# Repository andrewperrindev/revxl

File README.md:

# The RevXL Keyboard

The RevXL is a maximalist Reviung-inspired ergonomic keyboard with per-key RGB LEDs, an OLED display, a rotary encoder, and a breakaway arrow cluster. It’s powered by a wired RP2040 microcontroller with QMK and Vial handling things on the firmware side. At its core, the RevXL is designed to be an on ramp to the ergonomic mechanical keyboard space. It shows off the scene’s most catchy bells and whistles while still providing a few creature comforts of more traditional layouts.

## Sponsored By PCBWay

This project is sponsored by [PCBWay](https://www.pcbway.com). They're the internet's premier PCB fabricator and are a one-stop-shop for all your prototyping needs. They offer PCB fabrication services, 3D printing with a variety of materials, and even PCBA assembly services for those of you who prefer not to solder their own projects. If it can be represented as a design file, you can probably upload it to [PCBWay](https://www.pcbway.com) and receive it a few days later in the mail.

PCBWay did a great job manufacturing the RevXL PCB. The order shipped quickly, and all of the PCBs arrived safe and sound inside of a well packed box and vacuum sealed bubbled wrap. My thanks to [PCBWay](https://www.pcbway.com) for helping to make this keyboard a reality.

## Ergogen Layout

The RevXL was designed with the Ergogen keyboard layout generator. The techniques used here are similar to those I detailed in my [Ergogen tutorial series](https://flatfootfox.com/ergogen-introduction/). The largest new additions were the considerations needed for the per-key RGB LEDs and the breakaway arrow cluster.

## Custom Keycaps

I needed to order a few additional keycaps from [FK Caps](https://fkcaps.com/?a=FlatFootFox) to fill out the arrow key cluster. I decided to use that was an excuse to create a whole custom keycap layout. It's based around a minimalist 3x3 pixel font. You can *just* make out the key glyphs if you squint.

## Build of Materials

| Part                         | Amount | Price           | Link                                                 |
| ---------------------------- | ------ | --------------- | ---------------------------------------------------- |
| Revxl PCB via PCBWay         | 1      | $60.00 USD Shipped | https://github.com/ImStuBTW/revxl                    |
| RP2040 "Pro Micro"           | 1      | $3.00 USD       | https://www.aliexpress.us/item/3256806423363289.html |
| Choc Switches                | 68     | $40.00 USD      | https://www.aliexpress.us/item/3256805697157410.html |
| 1N4148 T4 Diodes             | 68     | $2.00 USD       | https://www.aliexpress.us/item/2255800498728983.html |
| SK6812 MINI-E RGB LEDs       | 68     | $2.00 USD       | https://www.aliexpress.us/item/2255800498728983.html |
| EC11 Rotary Encoder          | 1      | $2.50 USD       | https://www.aliexpress.us/item/2255800160725313.html |
| EC11 20x15mm Knob            | 1      | $3.00 USD       | https://www.aliexpress.us/item/2251832562966356.html |
| MBK Glow Keycaps             | 1      | $55.00 USD      | https://lowprokb.ca/collections/keycaps/products/mbk-glow-r2-keycap-sets |
| 6mm x 3mm x 4.3mm Pushbutton | 1     | $2.00 USD       | https://www.aliexpress.us/item/3256801663262003.html |
| Machine Pins                 | 35     | $6.00 USD       | https://www.aliexpress.us/item/3256801663262003.html |
| Machine Pin Headers          | 39     | $4.00 USD       | https://www.aliexpress.us/item/3256801663262003.html |
| 4mm M2 Screws                | 8      | $1.00 USD       | https://www.aliexpress.us/item/2255801062616407.html |
| 2mm M2 Screw Inserts         | 8      | $1.50 USD       | https://www.aliexpress.us/item/3256804349544912.html |
| Bumpons                      | 1 Pack | $1.00 USD       | https://www.aliexpress.us/item/3256804119199524.html |

# References and Footprints

The [Reviung](https://github.com/gtips/reviung) layout concept was based after gtips' original design. The split thumb design was inspired heavily by Pete Johanson's [revxlp](https://gitlab.com/lpgalaxy/revxlp). For a similar keyboard design available in kit form without the arrow keys, please check out 42Keeb's excellent [Rev57LP](https://42keebs.eu/shop/kits/pro-micro-based/rev57lp-50-low-profile-hotswap-ergo-kit/). They've added RGB LED support in the time it took me to create this keyboard.

The breakaway arrow cluster concept was inspired by the Afternoon Labs [Breeze](https://www.afternoonlabs.com/breeze/) keyboard.

Thanks to Moonbase for the [pixel font breakdown](https://moonbench.xyz/projects/tiny-pixel-art-fonts/)! 

Cheers to Ceoloide's [Ergogen-Footprints](https://github.com/ceoloide/ergogen-footprints) repo. There's more elegant ways of including it as a local git submodule. I may have just chucked their diode, display, LED, reset switch, rotary encoder, and Choc switch footprints into my `/footprints` folder.

The RP2040 footprint was based off rroel's [KiCAD footprint](https://github.com/rroels/kicad_pro_micro_rp2040).

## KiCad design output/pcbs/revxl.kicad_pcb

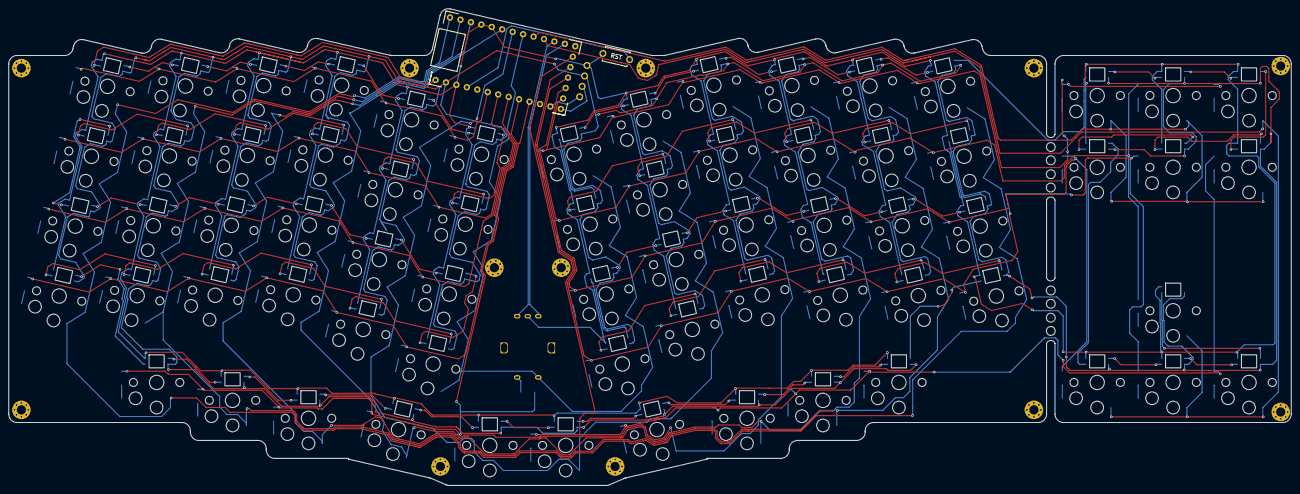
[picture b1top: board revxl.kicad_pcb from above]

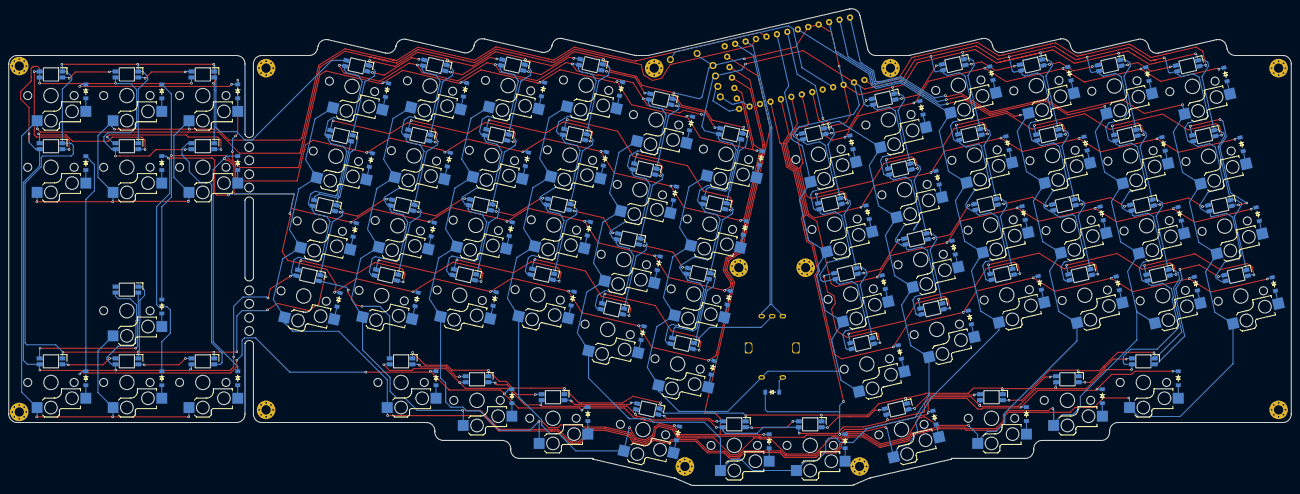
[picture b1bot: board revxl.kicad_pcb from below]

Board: 2 copper layers, 304.0 x 113.0 mm, 228 parts (205 on the bottom side), 156 nets.

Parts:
D1, D2, D3, D4, D5, D6, D7, D8, D9, D10, D11, D12, D13, D14, D15, D16, D17, D18, D19, D20, D21, D22, D23, D24, D25, D26, D27, D28, D29, D30, D31, D32, D33, D34, D35, D36, D37, D38, D39, D40, D41, D42, D43, D44, D45, D46, D47, D48, D49, D50, D51, D52, D53, D54, D55, D56, D57, D58, D59, D60, D61, D62, D63, D64, D65, D66, D67, D68, D69: diode_tht_sod123
DISP1: display_ssd1306
LED1, LED2, LED3, LED4, LED5, LED6, LED7, LED8, LED9, LED10, LED11, LED12, LED13, LED14, LED15, LED16, LED17, LED18, LED19, LED20, LED21, LED22, LED23, LED24, LED25, LED26, LED27, LED28, LED29, LED30, LED31, LED32, LED33, LED34, LED35, LED36, LED37, LED38, LED39, LED40, LED41, LED42, LED43, LED44, LED45, LED46, LED47, LED48, LED49, LED50, LED51, LED52, LED53, LED54, LED55, LED56, LED57, LED58, LED59, LED60, LED61, LED62, LED63, LED64, LED65, LED66, LED67, LED68: led_SK6812mini-e (per-keysingle-side)
RE1: rotary_encoder_ec11_ec12
RST1: reset_switch_tht_top
S1, S2, S3, S4, S5, S6, S7, S8, S9, S10, S11, S12, S13, S14, S15, S16, S17, S18, S19, S20, S21, S22, S23, S24, S25, S26, S27, S28, S29, S30, S31, S32, S33, S34, S35, S36, S37, S38, S39, S40, S41, S42, S43, S44, S45, S46, S47, S48, S49, S50, S51, S52, S53, S54, S55, S56, S57, S58, S59, S60, S61, S62, S63, S64, S65, S66, S67, S68: switch_choc_v1_v2
_1, _2, _3, _4, _5, _6, _7, _8, _9, _10, _11, _12, _13, _14, _15, _16, _17, _18, _19, _20: MountingHole_2.2mm_M2_Pad_Via

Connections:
GND: DISP1.4, LED1.3, LED2.3, LED3.3, LED4.3, LED5.3, LED6.3, LED7.3, LED8.3, LED9.3, LED10.3, LED11.3, LED12.3, LED13.3, LED14.3, LED15.3, LED16.3, LED17.3, LED18.3, LED19.3, LED20.3, LED21.3, LED22.3, LED23.3, LED24.3, LED25.3, LED26.3, LED27.3, LED28.3, LED29.3, LED30.3, LED31.3, LED32.3, LED33.3, LED34.3, LED35.3, LED36.3, LED37.3, LED38.3, LED39.3, LED40.3, LED41.3, LED42.3, LED43.3, LED44.3, LED45.3, LED46.3, LED47.3, LED48.3, LED49.3, LED50.3, LED51.3, LED52.3, LED53.3, LED54.3, LED55.3, LED56.3, LED57.3, LED58.3, LED59.3, LED60.3, LED61.3, LED62.3, LED63.3, LED64.3, LED65.3, LED66.3, LED67.3, LED68.3, RE1.B, RST1.2
LED1: LED4.2, LED8.4
LED2: LED8.2, LED12.4
LED3: LED12.2, LED16.4
LED4: LED16.2, LED20.4
LED5: LED20.2, LED24.4
LED6: LED23.4, LED24.2
LED7: LED19.4, LED23.2
LED8: LED15.4, LED19.2
LED9: LED11.4, LED15.2
LED10: LED7.4, LED11.2
LED11: LED3.4, LED7.2
LED12: LED2.4, LED3.2
LED13: LED2.2, LED6.4
LED14: LED6.2, LED10.4
LED15: LED10.2, LED14.4
LED16: LED14.2, LED18.4
LED17: LED18.2, LED22.4
LED18: LED21.4, LED22.2
LED19: LED17.4, LED21.2
LED20: LED13.4, LED17.2
LED21: LED9.4, LED13.2
LED22: LED5.4, LED9.2
LED23: LED1.4, LED5.2
LED24: LED1.2, LED49.4
LED25: LED49.2, LED50.4
LED26: LED50.2, LED51.4
LED27: LED51.2, LED55.4
LED28: LED55.2, LED57.4
LED29: LED57.2, LED58.4
LED30: LED56.4, LED58.2
LED31: LED54.4, LED56.2
LED32: LED53.4, LED54.2
LED33: LED52.4, LED53.2
LED34: LED25.4, LED52.2
LED35: LED25.2, LED29.4
LED36: LED29.2, LED33.4
LED37: LED33.2, LED37.4
LED38: LED37.2, LED41.4
LED39: LED41.2, LED45.4
LED40: LED45.2, LED46.4
LED41: LED42.4, LED46.2
LED42: LED38.4, LED42.2
LED43: LED34.4, LED38.2
LED44: LED30.4, LED34.2
LED45: LED26.4, LED30.2
LED46: LED26.2, LED27.4
LED47: LED27.2, LED31.4
LED48: LED31.2, LED35.4
LED49: LED35.2, LED39.4
LED50: LED39.2, LED43.4
LED51: LED43.2, LED47.4
LED52: LED47.2, LED48.4
LED53: LED44.4, LED48.2
LED54: LED40.4, LED44.2
LED55: LED36.4, LED40.2
LED56: LED32.4, LED36.2
LED57: LED28.4, LED32.2
LED58: LED28.2, LED61.4
LED59: LED61.2, LED65.4
LED60: LED65.2, LED68.4
LED61: LED67.4, LED68.2
LED62: LED64.4, LED67.2
LED63: LED60.4, LED64.2
LED64: LED59.4, LED60.2
LED65: LED59.2, LED62.4
LED66: LED62.2, LED66.4
LED67: LED63.4, LED66.2
VCC: DISP1.3, LED1.1, LED2.1, LED3.1, LED4.1, LED5.1, LED6.1, LED7.1, LED8.1, LED9.1, LED10.1, LED11.1, LED12.1, LED13.1, LED14.1, LED15.1, LED16.1, LED17.1, LED18.1, LED19.1, LED20.1, LED21.1, LED22.1, LED23.1, LED24.1, LED25.1, LED26.1, LED27.1, LED28.1, LED29.1, LED30.1, LED31.1, LED32.1, LED33.1, LED34.1, LED35.1, LED36.1, LED37.1, LED38.1, LED39.1, LED40.1, LED41.1, LED42.1, LED43.1, LED44.1, LED45.1, LED46.1, LED47.1, LED48.1, LED49.1, LED50.1, LED51.1, LED52.1, LED53.1, LED54.1, LED55.1, LED56.1, LED57.1, LED58.1, LED59.1, LED60.1, LED61.1, LED62.1, LED63.1, LED64.1, LED65.1, LED66.1, LED67.1, LED68.1
alt_modrow: D50.2, S50.2
center_del: D64.2, S64.2
center_down: D62.2, S62.2
center_ins: D65.2, S65.2
center_up: D63.2, S63.2
col0: S1.1, S2.1, S3.1, S4.1, S25.1, S26.1, S27.1, S28.1, S49.1, S52.1
col1: S5.1, S6.1, S7.1, S8.1, S29.1, S30.1, S31.1, S32.1, S50.1, S53.1
col2: S9.1, S10.1, S11.1, S12.1, S33.1, S34.1, S35.1, S36.1, S51.1, S54.1
col3: S13.1, S14.1, S15.1, S16.1, S37.1, S38.1, S39.1, S40.1, S55.1, S56.1
col4: S17.1, S18.1, S19.1, S20.1, S41.1, S42.1, S43.1, S44.1, S57.1, S58.1
col5: RE1.S1, S21.1, S22.1, S23.1, S24.1, S45.1, S46.1, S47.1, S48.1
col6: S60.1, S61.1, S64.1, S65.1, S67.1
col7: S59.1, S62.1, S63.1, S66.1, S68.1
ctrl_modrow: D49.2, S49.2
endiode: D69.2, RE1.S2
index_bottom: D17.2, S17.2
index_home: D18.2, S18.2
index_num: D20.2, S20.2
index_top: D19.2, S19.2
inner_bottom: D21.2, S21.2
inner_home: D22.2, S22.2
inner_num: D24.2, S24.2
inner_top: D23.2, S23.2
layercol_layerrow: D55.2, S55.2
left_del: D60.2, S60.2
left_down: D59.2, S59.2
left_ins: D61.2, S61.2
middle_bottom: D13.2, S13.2
middle_home: D14.2, S14.2
middle_num: D16.2, S16.2
middle_top: D15.2, S15.2
mirror_alt_modrow: D53.2, S53.2
mirror_ctrl_modrow: D52.2, S52.2
mirror_index_bottom: D41.2, S41.2
mirror_index_home: D42.2, S42.2
mirror_index_num: D44.2, S44.2
mirror_index_top: D43.2, S43.2
mirror_inner_bottom: D45.2, S45.2
mirror_inner_home: D46.2, S46.2
mirror_inner_num: D48.2, S48.2
mirror_inner_top: D47.2, S47.2
mirror_layercol_layerrow: D56.2, S56.2
mirror_middle_bottom: D37.2, S37.2
mirror_middle_home: D38.2, S38.2
mirror_middle_num: D40.2, S40.2
mirror_middle_top: D39.2, S39.2
mirror_outer_bottom: D25.2, S25.2
mirror_outer_home: D26.2, S26.2
mirror_outer_num: D28.2, S28.2
mirror_outer_top: D27.2, S27.2
mirror_pinky_bottom: D29.2, S29.2
mirror_pinky_home: D30.2, S30.2
mirror_pinky_num: D32.2, S32.2
mirror_pinky_top: D31.2, S31.2
mirror_ring_bottom: D33.2, S33.2
mirror_ring_home: D34.2, S34.2
mirror_ring_num: D36.2, S36.2
mirror_ring_top: D35.2, S35.2
mirror_spacecol_spacerow: D58.2, S58.2
mirror_super_modrow: D54.2, S54.2
outer_bottom: D1.2, S1.2
outer_home: D2.2, S2.2
outer_num: D4.2, S4.2
outer_top: D3.2, S3.2
pinky_bottom: D5.2, S5.2
pinky_home: D6.2, S6.2
pinky_num: D8.2, S8.2
pinky_top: D7.2, S7.2
right_del: D67.2, S67.2
right_down: D66.2, S66.2
right_ins: D68.2, S68.2
ring_bottom: D9.2, S9.2
ring_home: D10.2, S10.2
ring_num: D12.2, S12.2
ring_top: D11.2, S11.2
row0: D4.1, D8.1, D12.1, D16.1, D20.1, D24.1
row1: D3.1, D7.1, D11.1, D15.1, D19.1, D23.1
row2: D2.1, D6.1, D10.1, D14.1, D18.1, D22.1
row3: D1.1, D5.1, D9.1, D13.1, D17.1, D21.1
row4: D49.1, D50.1, D51.1, D55.1, D57.1, D69.1
row5: D28.1, D32.1, D36.1, D40.1, D44.1, D48.1, D61.1, D68.1
row6: D27.1, D31.1, D35.1, D39.1, D43.1, D47.1, D63.1, D65.1
row7: D26.1, D30.1, D34.1, D38.1, D42.1, D46.1, D59.1, D60.1
row8: D25.1, D29.1, D33.1, D37.1, D41.1, D45.1, D62.1, D64.1
row9: D52.1, D53.1, D54.1, D56.1, D58.1, D66.1, D67.1
spacecol_spacerow: D57.2, S57.2
super_modrow: D51.2, S51.2

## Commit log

2025-01-08 Init Commit
2025-01-08 Added keycap preview.
2025-01-08 Added FK Caps link.
2025-01-09 Added Ergogen Screenshot
2025-01-11 Rewired. Added case.
2025-01-11 Fixed Readme.
2025-01-29 Added QMK Firmware
2025-02-14 Firmware updates.
    Added Vial support.
2025-02-15 Fixed Image URL
2025-02-15 Fixed Readme
2025-02-15 Fixed Typo
2025-02-15 Fixed typos.
2025-03-06 Fixed Vial Mapping
2025-03-11 Customize Defaults & Macros
2025-03-15 Custom effect start
2025-03-15 Toggle effect based on layer
2025-03-17 More layer specific keys
2025-03-17 Use hue instead of rgb
2025-06-15 Add numpad operators and colors
